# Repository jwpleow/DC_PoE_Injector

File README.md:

# 802.3at PoE Injector, Mode B, with 12-32Vdc Input

It's too hard to find a midspan injector that takes in DC voltage.. (e.g. Phihong POE30D-1ATP-R / POE20D-1AF-R is a little hard to get a hold of)   

Disclaimer: Amateur hobbyist-grade work. I've got it printed and assembled by JLCPCB and used it successfully.

## JLCPCB Manufacturing Notes
Designed for the 4 Layer `JLC04161H-7628` - For 100Ohm impedance - 0.127mm trace spacing, 0.1402mm trace width

## Core Components

### Ethernet
| Part Name | Description | Datasheet | JLCPCB |
| - | - | - | - |
| TPS23861 | 802.3at Quad Port Power-over-Ethernet PSE Controller | [Datasheet](https://www.ti.com/lit/ds/symlink/tps23861.pdf)  | [JLCPCB](https://jlcpcb.com/partdetail/TexasInstruments-TPS23861PWR/C93245) | 
| SM51625EL | LAN 10/100/1000 Base-T (PoE++) Transformer | [Datasheet](https://wmsc.lcsc.com/wmsc/upload/file/pdf/v2/lcsc/2306061201_BOURNS-SM51625EL_C5357757.pdf) | [JLCPCB](https://jlcpcb.com/partdetail/Bourns-SM51625EL/C5357757) |
| R-RJ45R08P-C000 | RJ45, Horizontal, Shielded with LED | [Datasheet](https://wmsc.lcsc.com/wmsc/upload/file/pdf/v2/lcsc/1912111437_Ckmtw-Shenzhen-Cankemeng-R-RJ45R08P-C000_C386757.pdf) | [JLCPCB](https://jlcpcb.com/partdetail/360864-R_RJ45R08PC000/C386757) |

### Power
| Part Name | Description | Datasheet | JLCPCB |
| - | - | - | - |
| TPS7B8233QDGNRQ1 | 2.5-40V input, 3.3V 300mA output LDO | [Datasheet](https://www.ti.com/lit/ds/symlink/tps7b82-q1.pdf)  | [JLCPCB](https://jlcpcb.com/partdetail/TexasInstruments-TLV709A33DBVR/C21574006 ) | 
| LM5155QDSSRQ1 | Boost Converter | [Datasheet](https://www.ti.com/lit/ds/symlink/lm5155-q1.pdf) | [JLCPCB](https://jlcpcb.com/partdetail/TexasInstruments-LM5155QDSSRQ1/C1849528) |

## References
- [TPS23861 Datasheet](https://www.ti.com/lit/ds/symlink/tps23861.pdf)
- [TPS23861 Evaluation Module](https://www.ti.com/lit/ug/sluuay8e/sluuay8e.pdf)
- [TPS23861 Power-On Considerations](https://www.ti.com/lit/an/slva723/slva723.pdf)
- [MAX5945EV Kit](https://www.analog.com/media/en/technical-documentation/data-sheets/MAX5945EVKIT-MAX5945EVSYS.pdf)

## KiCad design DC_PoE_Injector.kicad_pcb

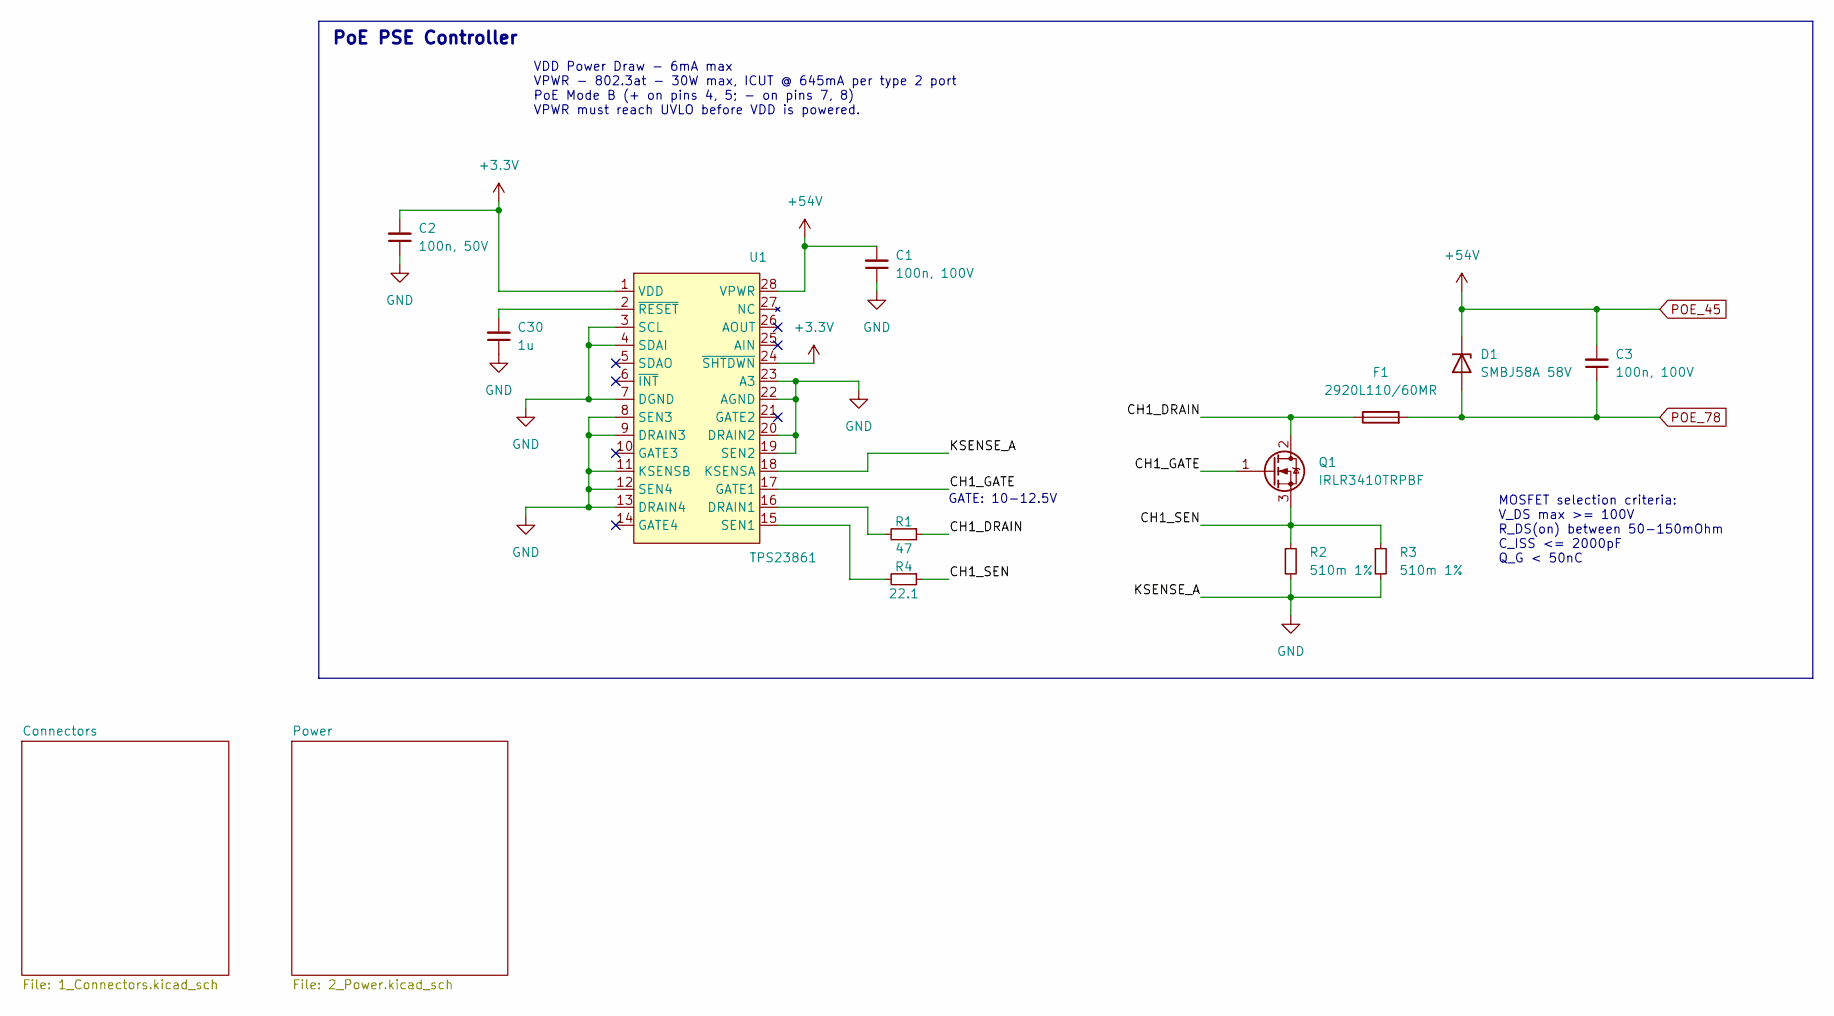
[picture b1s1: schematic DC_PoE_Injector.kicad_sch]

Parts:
C1, C3: 100n, 100V; C_0805_2012Metric; LCSC C28233
C2: 100n, 50V; C_0603_1608Metric; LCSC C14663
C30: 1u; C_0805_2012Metric; LCSC C28323
D1: SMBJ58A 58V; D_SMB; LCSC C135085
F1: 2920L110/60MR; Fuse_2920_7451Metric; LCSC C315903
Q1: IRLR3410TRPBF; TO-252-2-JLCPCB; LCSC C3017
R1: 47; R_0603_1608Metric; LCSC C23182
R2, R3: 510m 1%; R_0805_2012Metric; LCSC C491234
R4: 22.1; R_0603_1608Metric; LCSC C22958
U1: TPS23861; LCSC C93245

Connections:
+3.3V: C2.2, U1.1 (VDD), U1.24 (~SHTDWN); also elsewhere on the board
/CH1_DRAIN: F1.1, Q1.2 (D), R1.1
/CH1_GATE: Q1.1 (G), U1.17 (GATE1)
/CH1_SEN: Q1.3 (S), R2.1, R3.1, R4.1
GND: C1.1, C2.1, C30.1, R2.2, R3.2, U1.3 (SCL), U1.4 (SDAI), U1.7 (DGND), U1.8 (SEN3), U1.9 (DRAIN3), U1.11 (KSENSB), U1.12 (SEN4), U1.13 (DRAIN4), U1.18 (KSENSA), U1.19 (SEN2), U1.20 (DRAIN2), U1.22 (AGND), U1.23 (A3); also elsewhere on the board
unnamed: R1.2, U1.16 (DRAIN1)
unnamed: R4.2, U1.15 (SEN1)
unnamed: C30.2, U1.2 (~RESET)
POE_45: C1.2, C3.2, D1.1 (K), U1.28 (VPWR); also elsewhere on the board
POE_78: C3.1, D1.2 (A), F1.2; also elsewhere on the board

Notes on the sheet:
PoE PSE Controller
GATE: 10-12.5V
MOSFET selection criteria: V_DS max >= 100V R_DS(on) between 50-150mOhm C_ISS <= 2000pF Q_G < 50nC
VDD Power Draw - 6mA max VPWR - 802.3at - 30W max, ICUT @ 645mA per type 2 port PoE Mode B (+ on pins 4, 5; - on pins 7, 8) VPWR must reach UVLO before VDD is powered.

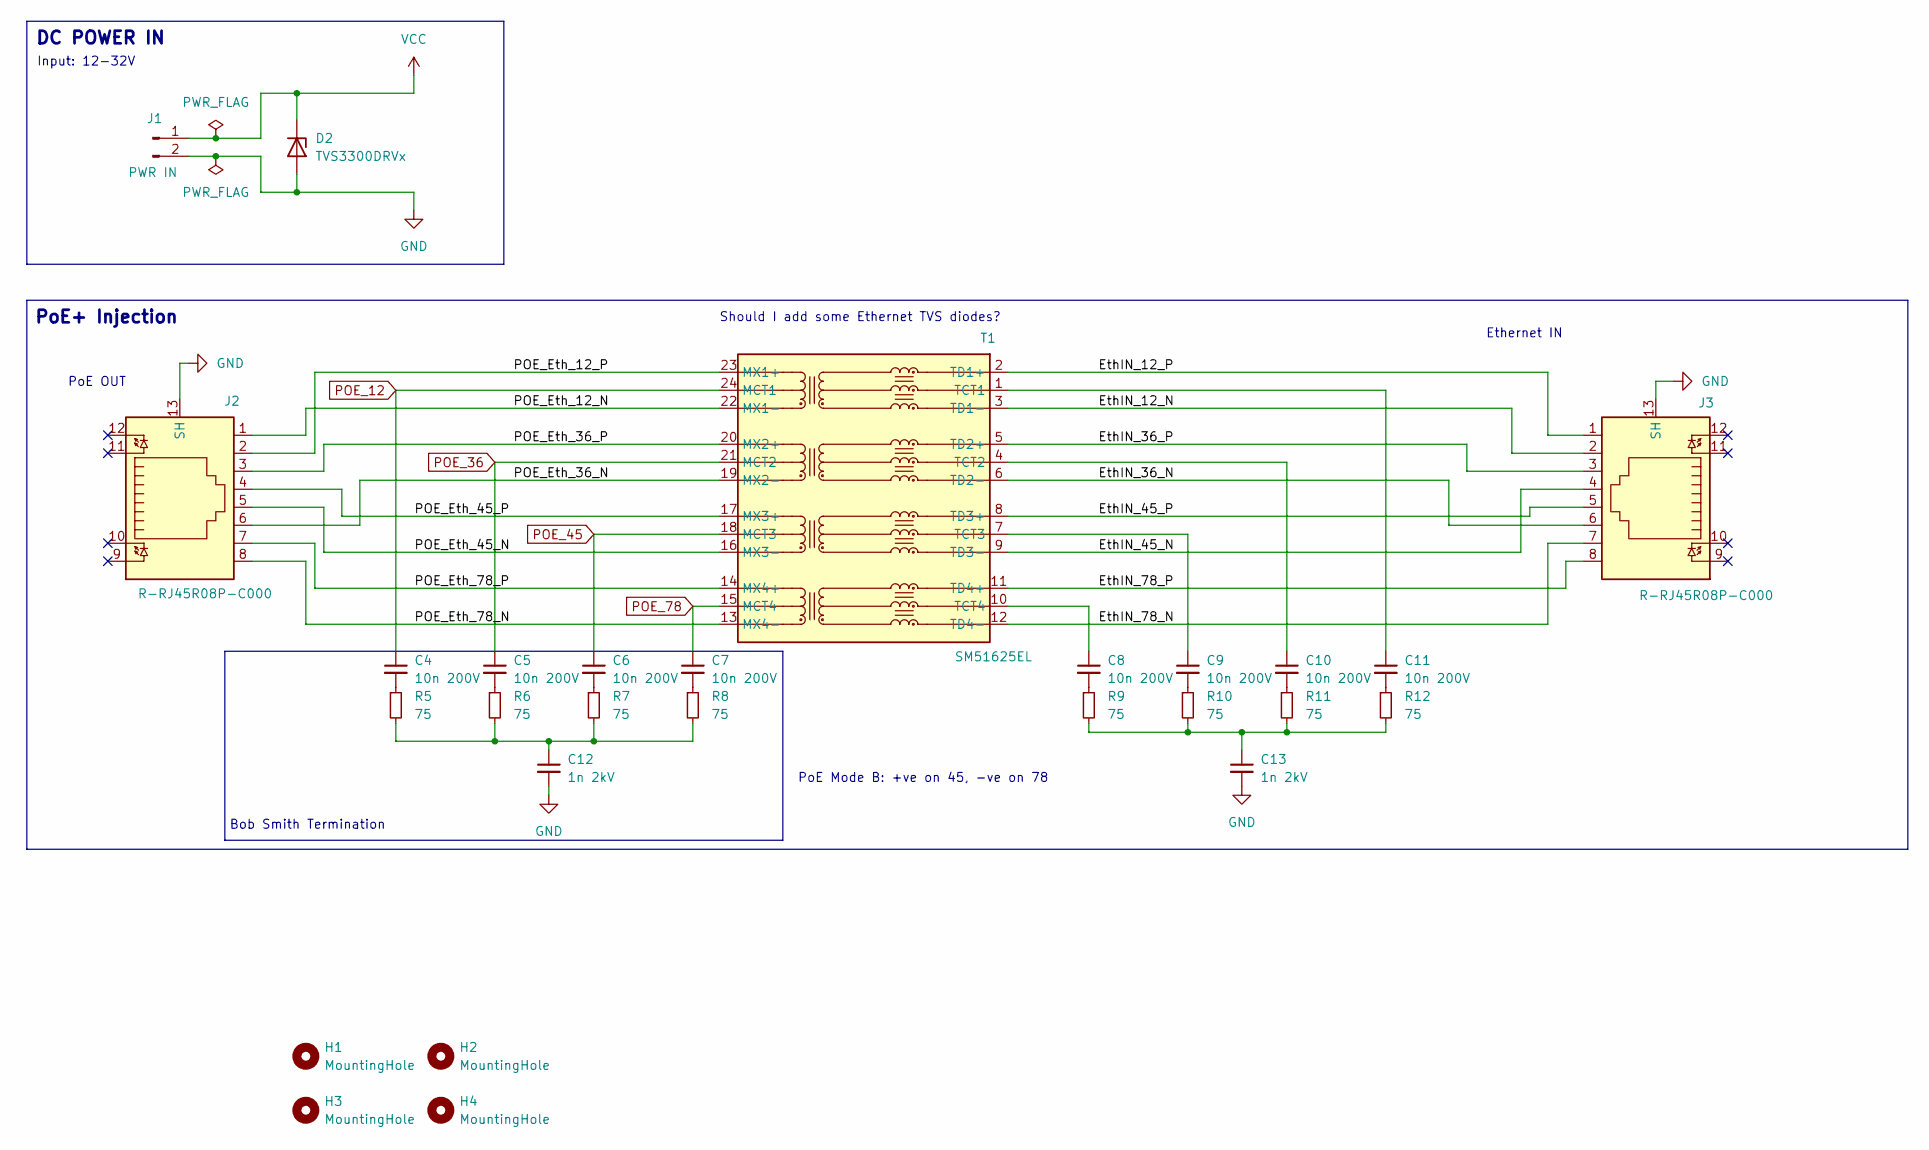
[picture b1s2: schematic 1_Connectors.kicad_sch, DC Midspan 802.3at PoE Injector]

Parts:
C4, C5, C6, C7, C8, C9, C10, C11: 10n 200V; C_0805_2012Metric; LCSC C106844
C12, C13: 1n 2kV; C_1206_3216Metric; LCSC C9196
D2: TVS3300DRVx; DRV0006A; LCSC C2863624
H1, H2, H3, H4: MountingHole; MountingHole_3.2mm_M3
J1: PWR IN; PhoenixContact_SPT_2.5_2-H-5.0_1x02_P5.0mm_Horizontal; LCSC C5443538
J2, J3: R-RJ45R08P-C000; LCSC C386757
R5, R6, R7, R8, R9, R10, R11, R12: 75; R_0805_2012Metric; LCSC C20638
T1: SM51625EL; Manufacturer_Part_Number SM51625EL; Mouser Part Number 652-SM51625EL

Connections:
/Connectors/EthIN_12_N: J3.2, T1.3 (TD1-)
/Connectors/EthIN_12_P: J3.1, T1.2 (TD1+)
/Connectors/EthIN_36_N: J3.6, T1.6 (TD2-)
/Connectors/EthIN_36_P: J3.3, T1.5 (TD2+)
/Connectors/EthIN_45_N: J3.4, T1.9 (TD3-)
/Connectors/EthIN_45_P: J3.5, T1.8 (TD3+)
/Connectors/EthIN_78_N: J3.7, T1.12 (TD4-)
/Connectors/EthIN_78_P: J3.8, T1.11 (TD4+)
/Connectors/POE_Eth_12_N: J2.1, T1.22 (MX1-)
/Connectors/POE_Eth_12_P: J2.2, T1.23 (MX1+)
/Connectors/POE_Eth_36_N: J2.6, T1.19 (MX2-)
/Connectors/POE_Eth_36_P: J2.3, T1.20 (MX2+)
/Connectors/POE_Eth_45_N: J2.5, T1.16 (MX3-)
/Connectors/POE_Eth_45_P: J2.4, T1.17 (MX3+)
/Connectors/POE_Eth_78_N: J2.8, T1.13 (MX4-)
/Connectors/POE_Eth_78_P: J2.7, T1.14 (MX4+)
GND: C12.2, C13.2, D2.1 (A), D2.2 (A), D2.3 (A), D2.7 (A), J1.2, J2.13 (SH), J3.13 (SH); also elsewhere on the board
unnamed: C4.2, R5.1
unnamed: C5.2, R6.1
unnamed: C6.2, R7.1
unnamed: C7.2, R8.1
unnamed: C8.2, R9.1
unnamed: C9.2, R10.1
unnamed: C10.2, R11.1
unnamed: C11.2, R12.1
unnamed: C12.1, R5.2, R6.2, R7.2, R8.2
unnamed: C13.1, R9.2, R10.2, R11.2, R12.2
unnamed: C11.1, T1.1 (TCT1)
unnamed: C10.1, T1.4 (TCT2)
unnamed: C9.1, T1.7 (TCT3)
unnamed: C8.1, T1.10 (TCT4)
POE_12: C4.1, T1.24 (MCT1)
POE_36: C5.1, T1.21 (MCT2)
POE_45: C6.1, T1.18 (MCT3); also elsewhere on the board
POE_78: C7.1, T1.15 (MCT4); also elsewhere on the board
VCC: D2.4 (K), D2.5 (K), D2.6 (K), J1.1; also elsewhere on the board

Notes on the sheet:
Input: 12-32V
PoE Mode B: +ve on 45, -ve on 78
PoE OUT
Ethernet IN
Should I add some Ethernet TVS diodes?
Bob Smith Termination
DC POWER IN
PoE+ Injection

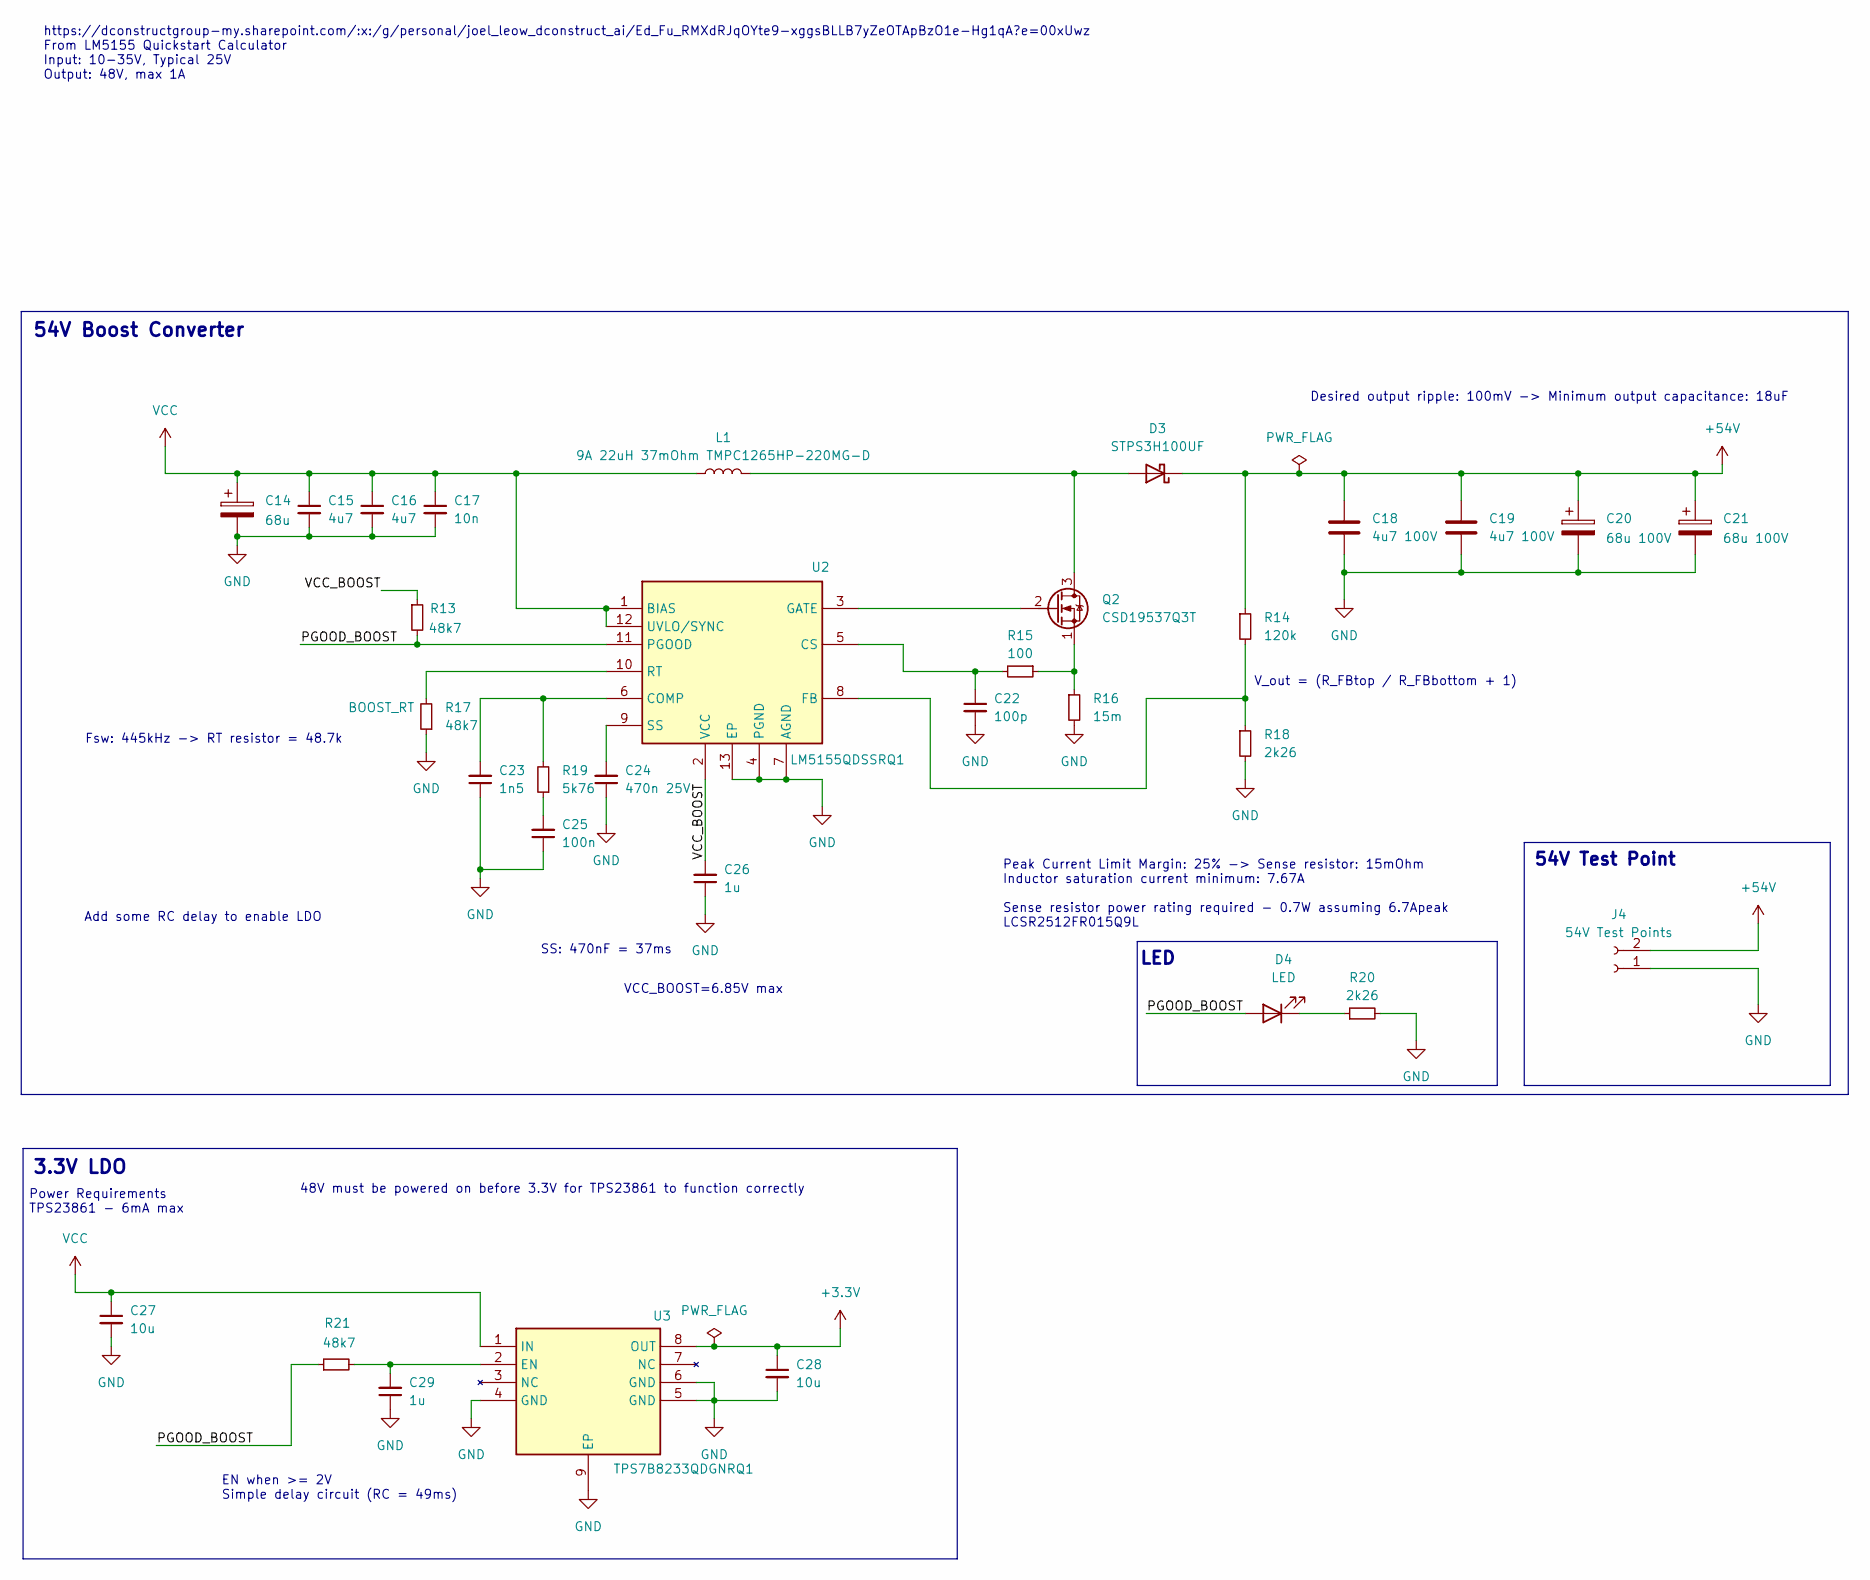
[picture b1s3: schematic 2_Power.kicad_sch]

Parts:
C14: 68u; CP_Elec_12.5x13.5; LCSC C278544
C15, C16: 4u7; C_1206_3216Metric; LCSC C29823
C17: 10n; C_0603_1608Metric; LCSC C57112
C18, C19: 4u7 100V; C_1210_3225Metric; LCSC C381466
C20, C21: 68u 100V; CP_Elec_12.5x13.5; LCSC C278544
C22: 100p; C_0402_1005Metric; LCSC C1546
C23: 1n5; R_0603_1608Metric; LCSC C1595
C24: 470n 25V; C_0603_1608Metric; LCSC C1623
C25: 100n; R_0603_1608Metric; LCSC C14663
C26, C29: 1u; C_0805_2012Metric; LCSC C28323
C27, C28: 10u; C_0805_2012Metric; LCSC C440198
D3: STPS3H100UF; D_SMBflat; LCSC C155643
D4: LED; LED_0603_1608Metric; LCSC C2286
J4: 54V Test Points; SolderWire-2.5sqmm_1x02_P8.8mm_D2.4mm_OD4.4mm
L1: 9A 22uH 37mOhm TMPC1265HP-220MG-D; L_TaiTech_TMPC1265_13.5x12.5mm; LCSC C305224
Q2: CSD19537Q3T
R13, R17, R21: 48k7; R_0402_1005Metric; LCSC C26981
R14: 120k; R_0603_1608Metric; LCSC C25808
R15: 100; R_0603_1608Metric; LCSC C22775
R16: 15m; R_2512_6332Metric; LCSC C520400
R18, R20: 2k26; R_0603_1608Metric; LCSC C22904
R19: 5k76; R_0603_1608Metric; LCSC C23070
U2: LM5155QDSSRQ1; DSS0012x; Manufacturer_Part_Number LM5155QDSSRQ1; Mouser Part Number 595-LM5155QDSSRQ1
U3: TPS7B8233QDGNRQ1; DGN0008G; Manufacturer_Part_Number TPS7B8233QDGNRQ1; Mouser Part Number 595-TPS7B8233QDGNRQ1

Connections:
+3.3V: C28.1, U3.8 (OUT); also elsewhere on the board
/Power/PGOOD_BOOST: D4.2 (A), R13.2, R21.1, U2.11 (PGOOD)
/Power/VCC_BOOST: C26.2, R13.1, U2.2 (VCC)
GND: C14.2, C15.2, C16.2, C17.2, C18.2, C19.2, C20.2, C21.2, C22.2, C23.1, C24.1, C25.1, C26.1, C27.2, C28.2, C29.1, J4.1, R16.2, R17.1, R18.2, R20.2, U2.4 (PGND), U2.7 (AGND), U2.13 (EP), U3.4 (GND), U3.5 (GND), U3.6 (GND), U3.9 (EP); also elsewhere on the board
unnamed: C25.2, R19.1
unnamed: D3.2 (A), L1.2, Q2.3 (D)
unnamed: D4.1 (K), R20.1
unnamed: Q2.2 (G), U2.3 (GATE)
unnamed: Q2.1 (S), R15.1, R16.1
unnamed: C23.2, R19.2, U2.6 (COMP)
unnamed: C22.1, R15.2, U2.5 (CS)
unnamed: R14.2, R18.1, U2.8 (FB)
unnamed: R17.2, U2.10 (RT)
unnamed: C24.2, U2.9 (SS)
unnamed: C29.2, R21.2, U3.2 (EN)
POE_45: C18.1, C19.1, C20.1, C21.1, D3.1 (K), J4.2, R14.1; also elsewhere on the board
VCC: C14.1, C15.1, C16.1, C17.1, C27.1, L1.1, U2.1 (BIAS), U2.12 (UVLO/SYNC), U3.1 (IN); also elsewhere on the board

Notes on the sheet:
SS: 470nF = 37ms
Desired output ripple: 100mV -> Minimum output capacitance: 18uF
V_out = (R_FBtop / R_FBbottom + 1)
LED
Power Requirements TPS23861 - 6mA max
54V Test Point
Fsw: 445kHz -> RT resistor = 48.7k
Add some RC delay to enable LDO
3.3V LDO
Peak Current Limit Margin: 25% -> Sense resistor: 15mOhm Inductor saturation current minimum: 7.67A Sense resistor power rating required - 0.7W assuming 6.7Apeak LCSR2512FR015Q9L
48V must be powered on before 3.3V for TPS23861 to function correctly
EN when >= 2V Simple delay circuit (RC = 49ms)
54V Boost Converter
https://dconstructgroup-my.sharepoint.com/:x:/g/personal/joel_leow_dconstruct_ai/Ed_Fu_RMXdRJqOYte9-xggsBLLB7yZeOTApBzO1e-Hg1qA?e=00xUwz From LM5155 Quickstart Calculator Input: 10-35V, Typical 25V Output: 48V, max 1A
VCC_BOOST=6.85V max

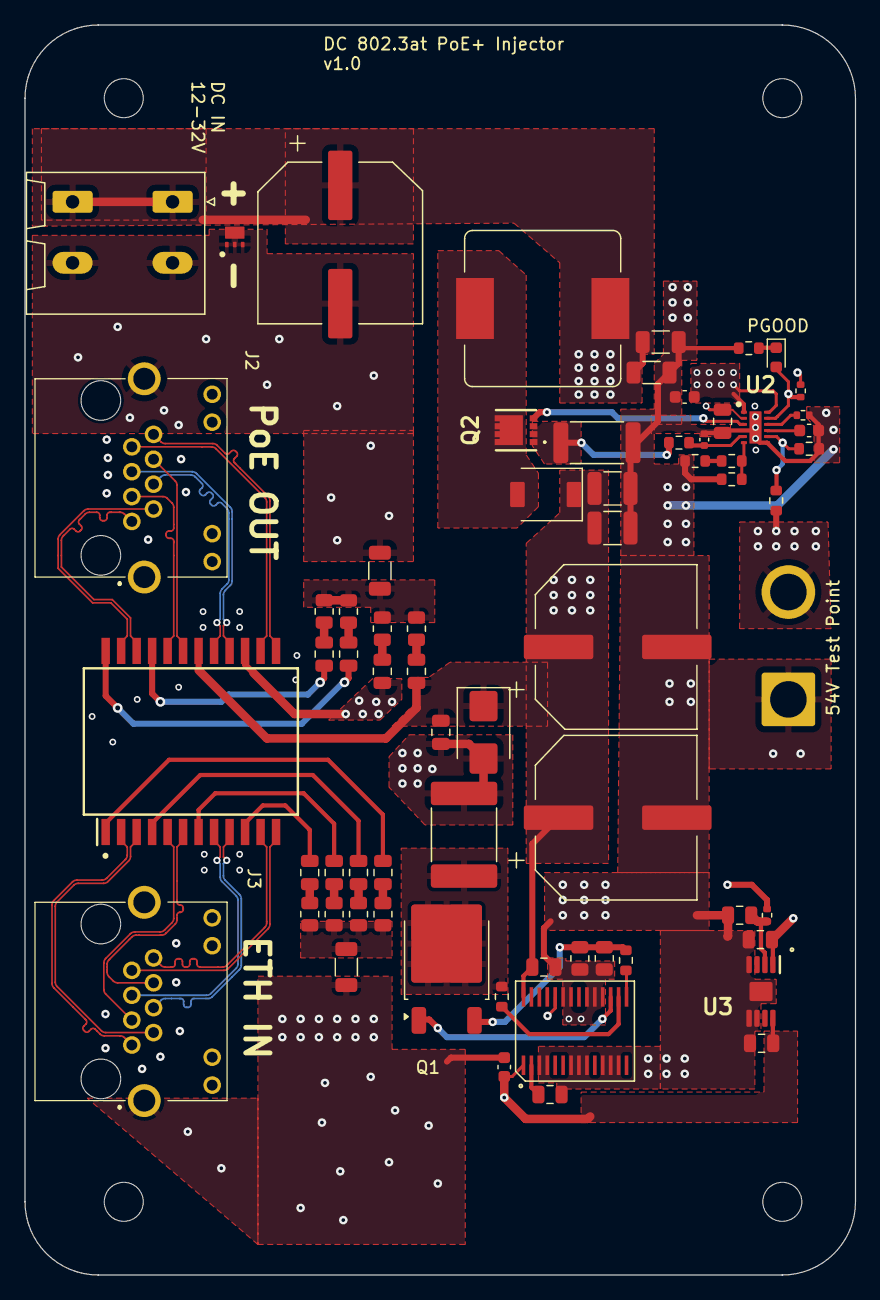
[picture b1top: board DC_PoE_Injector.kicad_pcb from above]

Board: 4 copper layers, 68.1 x 102.5 mm, 71 parts (0 on the bottom side), 56 nets.

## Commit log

2024-07-21 Add initial repo setup
2024-07-27 add readme
2024-07-27 Adding some skeleton
2024-07-28 Add magnetics for poe
2024-08-04 Add boost converter
2024-08-09 finish layout
2024-08-13 Some cleanups
2024-08-25 add silkscreen labels for power
2024-08-25 update kicadlib
2024-08-25 update readme again
2024-08-25 fix some outdated footprints
